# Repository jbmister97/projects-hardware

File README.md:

View this project on [CADLAB.io](https://cadlab.io/project/2418). 

# projects-hardware

A collection of personal schematics and PCB design projects done using various EDA tools. Most of the projects are done using KiCad software with the exceptions of the following projects:

Arduino_Nanite_85   - Altium CircuitMaker
      
These projects can be downloaded and viewed using their respective EDA tools.

NOTE: Some of these projects may be unfinished and the ones that are in progress may be found in a separate branch and not in master. Switch to that branch to view the project.

Finished:

-NRF52 Reference

      Known issue: Low battery indicator not functioning properly. It is on when battery is high and off when battery is low.
      
-Buck converter V1

-Outlet Relay V1

-USB Type A Breakout V1

In progress:

-NRF52 V2

-4-Channel Motor controller

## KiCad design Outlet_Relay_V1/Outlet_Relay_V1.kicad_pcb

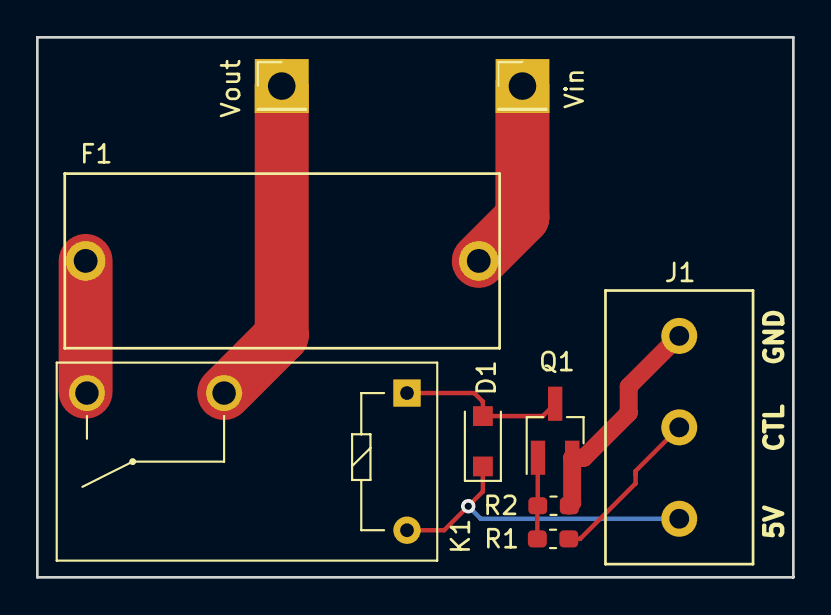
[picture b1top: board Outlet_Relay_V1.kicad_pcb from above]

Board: 2 copper layers, 42.0 x 30.0 mm, 9 parts (0 on the bottom side), 8 nets.

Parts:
D1: BAS116H,115; D_SOD-123F
F1: Fuse; Fuse_Holder_Keystone_4527_Cartridge
J1: TerminalBlock_1x3_5.08mmPitch; TerminalBlock_Molex_1x3_5.04mmPitch
K1: G5Q-1A; Relay_SPST_Omron-G5Q-1A
Q1: BSS138K; SOT-23_Handsoldering
R1: 1k; R_0603_1608Metric_Pad1.05x0.95mm_HandSolder
R2: 10k; R_0603_1608Metric_Pad1.05x0.95mm_HandSolder
Vin: PinHeader_1x01_P2.54mm_Vertical
Vout: PinHeader_1x01_P2.54mm_Vertical

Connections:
/5V: D1.1, J1.1, K1.5
/CTL: J1.2, R1.1
GND: J1.3, Q1.2, R2.2
unnamed: D1.2, K1.1, Q1.3
unnamed: F1.1, K1.3
unnamed: Q1.1, R1.2, R2.1
Vin: F1.2, Vin.1
Vout: K1.2, Vout.1

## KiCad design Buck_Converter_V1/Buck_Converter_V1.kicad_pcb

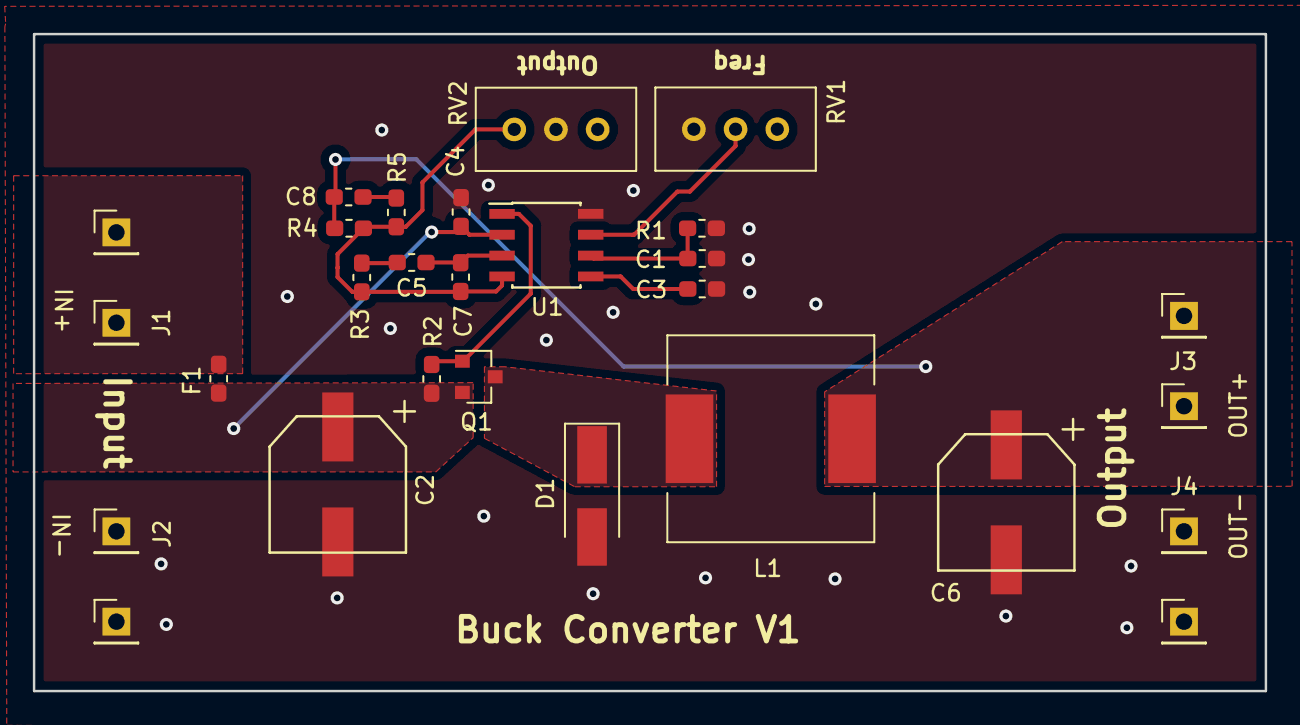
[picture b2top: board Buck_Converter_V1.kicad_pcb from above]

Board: 2 copper layers, 75.0 x 40.0 mm, 28 parts (0 on the bottom side), 13 nets.

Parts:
C1, C4: 0.1uF; C_0603_1608Metric_Pad1.05x0.95mm_HandSolder
C2, C6: 180uF; C_AlPo_Radial_SMT_8.3mmx8.3mm
C3: 1uF; C_0603_1608Metric_Pad1.05x0.95mm_HandSolder
C5: 6.8nF; C_0603_1608Metric_Pad1.05x0.95mm_HandSolder
C7: 68pF; C_0603_1608Metric_Pad1.05x0.95mm_HandSolder
C8: 4.7nF; C_0603_1608Metric_Pad1.05x0.95mm_HandSolder
D1: NRVTSA4100ET3G; D_SMA_Handsoldering
F1: Fuse; Fuse_0603_1608Metric_Pad1.05x0.95mm_HandSolder
IN+: PinHeader_1x01_P2.54mm_Vertical
IN-: PinHeader_1x01_P2.54mm_Vertical
J1, J2, J3, J4: Conn_01x01_Male; PinHeader_1x01_P2.54mm_Vertical
L1: 33uH; L_12x12mm_H8mm
OUT+: PinHeader_1x01_P2.54mm_Vertical
OUT-: PinHeader_1x01_P2.54mm_Vertical
Q1: SI2319CDS-T1-GE3; SOT-23
R1: 56k; R_0603_1608Metric_Pad1.05x0.95mm_HandSolder
R2: 3k; R_0603_1608Metric_Pad1.05x0.95mm_HandSolder
R3: 14.9k; R_0603_1608Metric_Pad1.05x0.95mm_HandSolder
R4: 16.5k; R_0603_1608Metric_Pad1.05x0.95mm_HandSolder
R5: 383; R_0603_1608Metric_Pad1.05x0.95mm_HandSolder
RV1: 25k; Potentiometer_Bourns_3296W_Vertical
RV2: 4125; Potentiometer_Bourns_3296W_Vertical
U1: TL5001CDR; SOIC-8_3.9x4.9mm_P1.27mm

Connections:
GND: C1.2, C2.2, C3.1, C4.2, C6.2, D1.2, IN-.1, J2.1, J4.1, OUT-.1, R1.2, RV1.1, RV2.2, U1.8
unnamed: C1.1, R1.1, U1.6
unnamed: C3.2, U1.5
unnamed: C5.1, R3.2
unnamed: C5.2, C7.2, U1.3
unnamed: C7.1, R3.1, R4.2, R5.2, RV2.1, U1.4
unnamed: C8.2, R5.1
unnamed: D1.1, L1.1, Q1.3
unnamed: F1.2, IN+.1, J1.1
unnamed: RV1.2, U1.7
P_DRIVE: Q1.1, R2.1, U1.1
Vin: C2.1, C4.1, F1.1, Q1.2, R2.2, U1.2
Vout: C6.1, C8.1, J3.1, L1.2, OUT+.1, R4.1

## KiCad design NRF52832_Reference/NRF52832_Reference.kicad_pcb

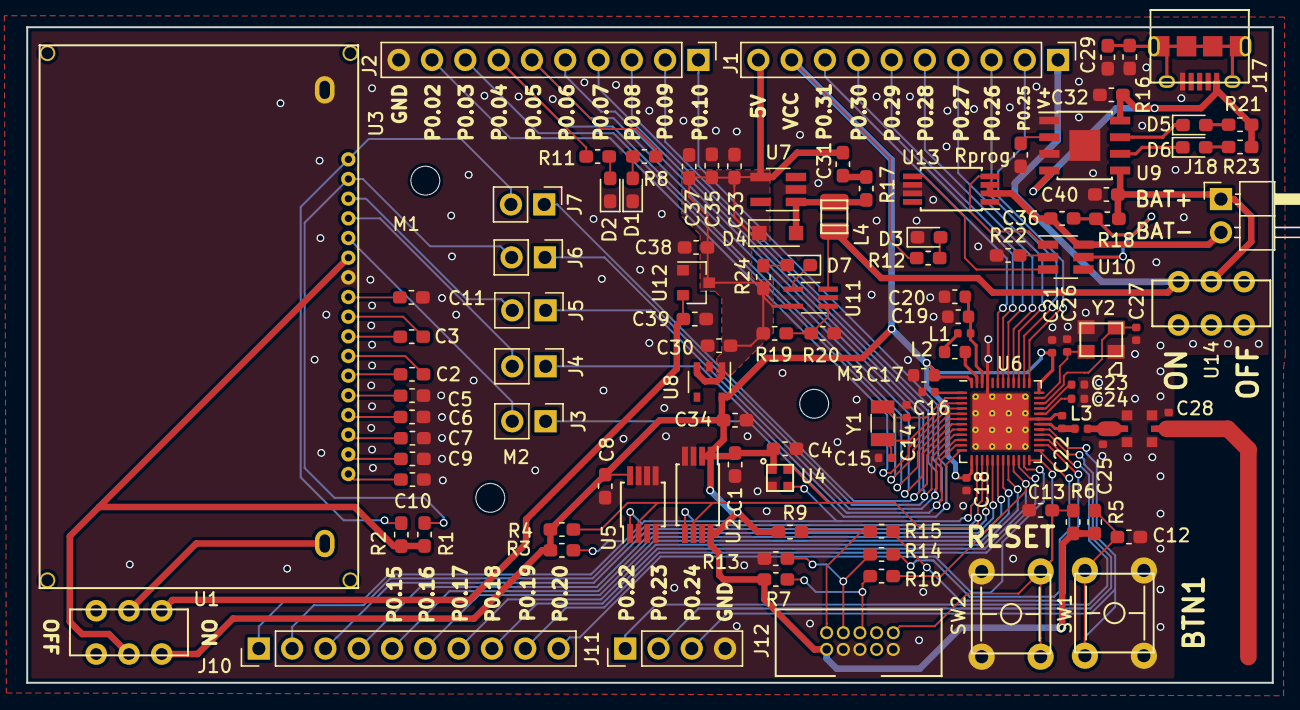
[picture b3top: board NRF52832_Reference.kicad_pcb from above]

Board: 2 copper layers, 95.0 x 50.0 mm, 110 parts (0 on the bottom side), 91 nets.

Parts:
C1, C4, C8, C12, C13, C29, C36: 0.1uF; C_0603_1608Metric_Pad1.05x0.95mm_HandSolder
C2, C3, C5, C6, C7, C9, C10, C11, C30, C34, C38: 1uF; C_0603_1608Metric_Pad1.05x0.95mm_HandSolder
C14, C15: 14pF; C_0402_1005Metric
C16, C18, C21: 100nF; C_0402_1005Metric
C17: 4.7uF; C_0603_1608Metric
C19: 1.0uF; C_0603_1608Metric
C20: N.C.; C_0603_1608Metric
C22: 0.8pF; C_0402_1005Metric
C23: 100pF; C_0402_1005Metric
C24, C25: N.C.; C_0402_1005Metric
C26: 12pF; C_0402_1005Metric
C27: 12nF; C_0402_1005Metric
C28: 1.2pF; C_0402_1005Metric
C31: 120pF; C_0603_1608Metric_Pad1.05x0.95mm_HandSolder
C32, C33, C35, C37, C40: 10uF; C_0603_1608Metric_Pad1.05x0.95mm_HandSolder
C39: 4.7uF; C_0603_1608Metric_Pad1.05x0.95mm_HandSolder
D1, D2, D3, D5, D6, D7: LED; LED_0603_1608Metric_Pad1.05x0.95mm_HandSolder
D4: D_Schottky; D_SOD-123F
J1, J2, J10: Conn_01x10_Male; PinHeader_1x10_P2.54mm_Vertical
J3, J4, J5, J6, J7: Conn_01x02_Male; PinHeader_1x02_P2.54mm_Vertical
J11: Conn_01x04_Male; PinHeader_1x04_P2.54mm_Vertical
J12: SWD_Header; SWD_Header_CNC_Tech_3220-10-0100-00
J16: MM8130-2600RA2; MURATA_MM8130-2600RA2
J17: USB_B_Micro; USB_Micro_B_Amphenol_10118194-0001LF
J18: Conn_01x02_Male; PinHeader_1x02_P2.54mm_Horizontal
L1: 15nH; L_0402_1005Metric
L2: 10uH; L_0603_1608Metric
L3: 3.9nH; L_0402_1005Metric
L4: 2.2uH; L_1008_2520Metric
M1, M2, M3: MountingHole_2.2mm_M2
R1, R2, R7, R9, R13, R16: 10k; R_0603_1608Metric_Pad1.05x0.95mm_HandSolder
R3, R4: 4.7k; R_0603_1608Metric_Pad1.05x0.95mm_HandSolder
R5, R6: 47k; R_0603_1608Metric_Pad1.05x0.95mm_HandSolder
R8, R11, R12, R18: 100; R_0603_1608Metric_Pad1.05x0.95mm_HandSolder
R10, R14, R15: 22; R_0603_1608Metric_Pad1.05x0.95mm_HandSolder
R17: 5.6; R_0603_1608Metric_Pad1.05x0.95mm_HandSolder
R19: 100k; R_0603_1608Metric_Pad1.05x0.95mm_HandSolder
R20: 220k; R_0603_1608Metric_Pad1.05x0.95mm_HandSolder
R21, R23: 300; R_0603_1608Metric_Pad1.05x0.95mm_HandSolder
R22: 1k; R_0603_1608Metric_Pad1.05x0.95mm_HandSolder
R24: 220; R_0603_1608Metric_Pad1.05x0.95mm_HandSolder
Rprog: 1.2k; R_0603_1608Metric_Pad1.05x0.95mm_HandSolder
SW1, SW2: Button; SW_Tactile_TE_1825910-6
U1, U14: SLIDE_SW_DPDT; SW_DPDT_Slide_JS202011CQN
U2: AT34C04-X5M-T; TSSOP-8_4.4x3mm_P0.65mm
U3: NHD-C12832A1Z-NSW-BBW-3V3; LCD_NHD-C12832A1Z-NSW-BBW-3V3
U4: LTR-329ALS-01; Sensor_Photo_LTR-329ALS-01
U5: TCN75AVUA713; MSOP-8_3x3mm_P0.65mm
U6: nRF52832; QFN-48-1EP_6x6mm_P0.4mm_EP4.3x4.3mm_ThermalVias
U7: TPS613222ADBVR; SOT-23-5_HandSoldering
U8: NCV8161BSN330T1G; TSOP-5_1.65x3.05mm_P0.95mm
U9: TP4056E-SN2L1P; SOIC-8-1EP_3.9x4.9mm_P1.27mm_EP2.35x2.35mm
U10: DW01; SOT-23-6_Handsoldering
U11: LMV331ICT; SOT-353_SC-70-5_Handsoldering
U12: AP2138N-3.0TRG1; SOT-23
U13: FS8205A; TSSOP-8_4.4x3mm_P0.65mm
Y1: 32.768kHz; Crystal_SMD_3215-2Pin_3.2x1.5mm
Y2: 32MHz; Crystal_32MHz_Kyocera_CX3225SB32000D0FFFCC

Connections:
3V3_Ref: C1.1, C4.1, C8.1, C17.1, C18.1, C21.1, C34.1, J1.9, J12.1, R3.1, R4.1, R5.1, R6.1, R7.1, R9.1, R12.1, U1.3, U2.1, U2.2, U2.8, U4.1, U5.8, U6.13, U6.36, U6.48, U8.5
3V_Ref: C39.1, U1.6, U12.2
5V_Ref: C30.1, C31.1, C33.1, C35.1, C37.1, C38.1, D4.1, J1.10, R19.1, R24.1, U7.4, U8.1, U8.3, U11.5, U12.3
/Sheet5BF15571/ANT: C28.1, J16.OUT
/Sheet5BF15571/RF: C25.1, J16.IN, L3.2
/Sheet5BF15571/SWDCLK: R14.2, U6.25
/Sheet5BF15571/SWDIO: R15.2, U6.26
GND: C1.2, C4.2, C5.2, C6.2, C7.2, C8.2, C9.2, C10.2, C11.2, C12.2, C13.2, C14.2, C15.2, C16.2, C17.2, C18.2, C19.2, C20.2, C21.2, C22.2, C23.1, C24.1, C25.2, C26.1, C27.1, C28.2, C29.2, C30.2, C32.2, C33.2, C34.2, C35.2, C37.2, C38.2, C39.2, C40.2, D1.1, D2.1, D3.1, J2.10, J11.4, J12.3, J12.5, J12.9, J16.GND1, J16.GND2, J16.GND3, J16.GND4, J17.5, R13.2, R16.2, R20.2, R22.2, Rprog.2, SW1.3, SW1.4, SW2.3, SW2.4, U2.3, U2.4, U3.11, U3.19, U4.2, U5.4, U5.5, U5.6, U5.7, U6.31, U6.45, U6.49, U7.2, U8.2, U9.1, U9.3, U9.9, U11.2, U12.1, U13.6, U13.7, Y2.2, Y2.4
unnamed: C2.1, U3.6
unnamed: C2.2, U3.7
unnamed: C3.1, U3.9
unnamed: C3.2, U3.8
unnamed: C5.1, U3.5
unnamed: C6.1, U3.4
unnamed: C7.1, U3.3
unnamed: C9.1, U3.2
unnamed: C10.1, U3.1
unnamed: C11.1, U3.10
unnamed: C14.1, U6.2, Y1.1
unnamed: C15.1, U6.3, Y1.2
unnamed: C16.1, U6.1
unnamed: C19.1, C20.1, L1.2, U6.46
unnamed: C22.1, L3.1, U6.30
unnamed: C23.2, U6.33
unnamed: C24.2, U6.32
unnamed: C26.2, U6.35, Y2.1
unnamed: C27.2, U6.34, Y2.3
unnamed: C29.1, J17.6, R16.1
unnamed: C31.2, R17.1
unnamed: C32.1, J17.1, R21.1, R23.1, U9.4, U9.8
unnamed: C36.1, R18.1, U10.5
unnamed: C36.2, J18.2, U10.6, U13.2, U13.3
unnamed: C40.1, J18.1, R18.2, U9.5, U14.2
unnamed: D1.2, R8.2
unnamed: D2.2, R11.2
unnamed: D3.2, R12.2
unnamed: D4.2, L4.2, R17.2, U7.1
unnamed: D5.1, U9.7
unnamed: D5.2, R21.2
unnamed: D6.1, U9.6
unnamed: D6.2, R23.2
unnamed: D7.1, U11.4
unnamed: D7.2, R24.2
unnamed: J3.2, U3.13
unnamed: J4.2, U3.14
unnamed: J5.2, U3.15
unnamed: J6.2, R1.2, U3.16
unnamed: J7.2, R2.2, U3.17
unnamed: J12.2, R9.2, R15.1
unnamed: J12.4, R13.1, R14.1
unnamed: J12.6, R7.2, R10.2
unnamed: L1.1, L2.2
unnamed: L2.1, U6.47
unnamed: R1.1, R2.1, U1.2, U3.12
unnamed: R19.2, R20.1, U11.1
unnamed: R22.1, U10.2
unnamed: Rprog.1, U9.2
unnamed: U1.5, U3.18
unnamed: U10.1, U13.4
unnamed: U10.3, U13.5
P0.02: J2.9, U6.4
P0.03: J2.8, U6.5
P0.04: J2.7, R11.1, U6.6
P0.05: J2.6, R8.1, U6.7
P0.06_CS1: J2.5, J7.1, U6.8
P0.07_RES: J2.4, J6.1, U6.9
P0.08_A0: J2.3, J5.1, U6.10
P0.09_SCL: J2.2, J4.1, U6.11
P0.10_SI: J2.1, J3.1, U6.12
P0.11_SDA: J10.1, R3.2, U2.5, U4.3, U5.1, U6.14
P0.12_SCL: J10.2, R4.2, U2.6, U4.4, U5.2, U6.15
P0.13: J10.3, U6.16
P0.14: J10.4, U6.17
P0.15: J10.5, U6.18
P0.16: J10.6, U6.19
P0.17: J10.7, U6.20
P0.18_SWO: J10.8, R10.1, U6.21
P0.19: J10.9, U6.22
P0.20: J10.10, U6.23
P0.22: J11.1, U6.27
P0.23: J11.2, U6.28
P0.24: C12.1, J11.3, R5.2, SW1.1, SW1.2, U6.29
P0.25: J1.2, U6.37
P0.26: J1.3, U6.38
P0.27: J1.4, U6.39
P0.28: J1.5, U6.40
P0.29: J1.6, U6.41
P0.30: J1.7, U6.42
P0.31: J1.8, U6.43
RESET: C13.1, J12.10, R6.2, SW2.1, SW2.2, U6.24
V+: J1.1, L4.1, U11.3, U14.3

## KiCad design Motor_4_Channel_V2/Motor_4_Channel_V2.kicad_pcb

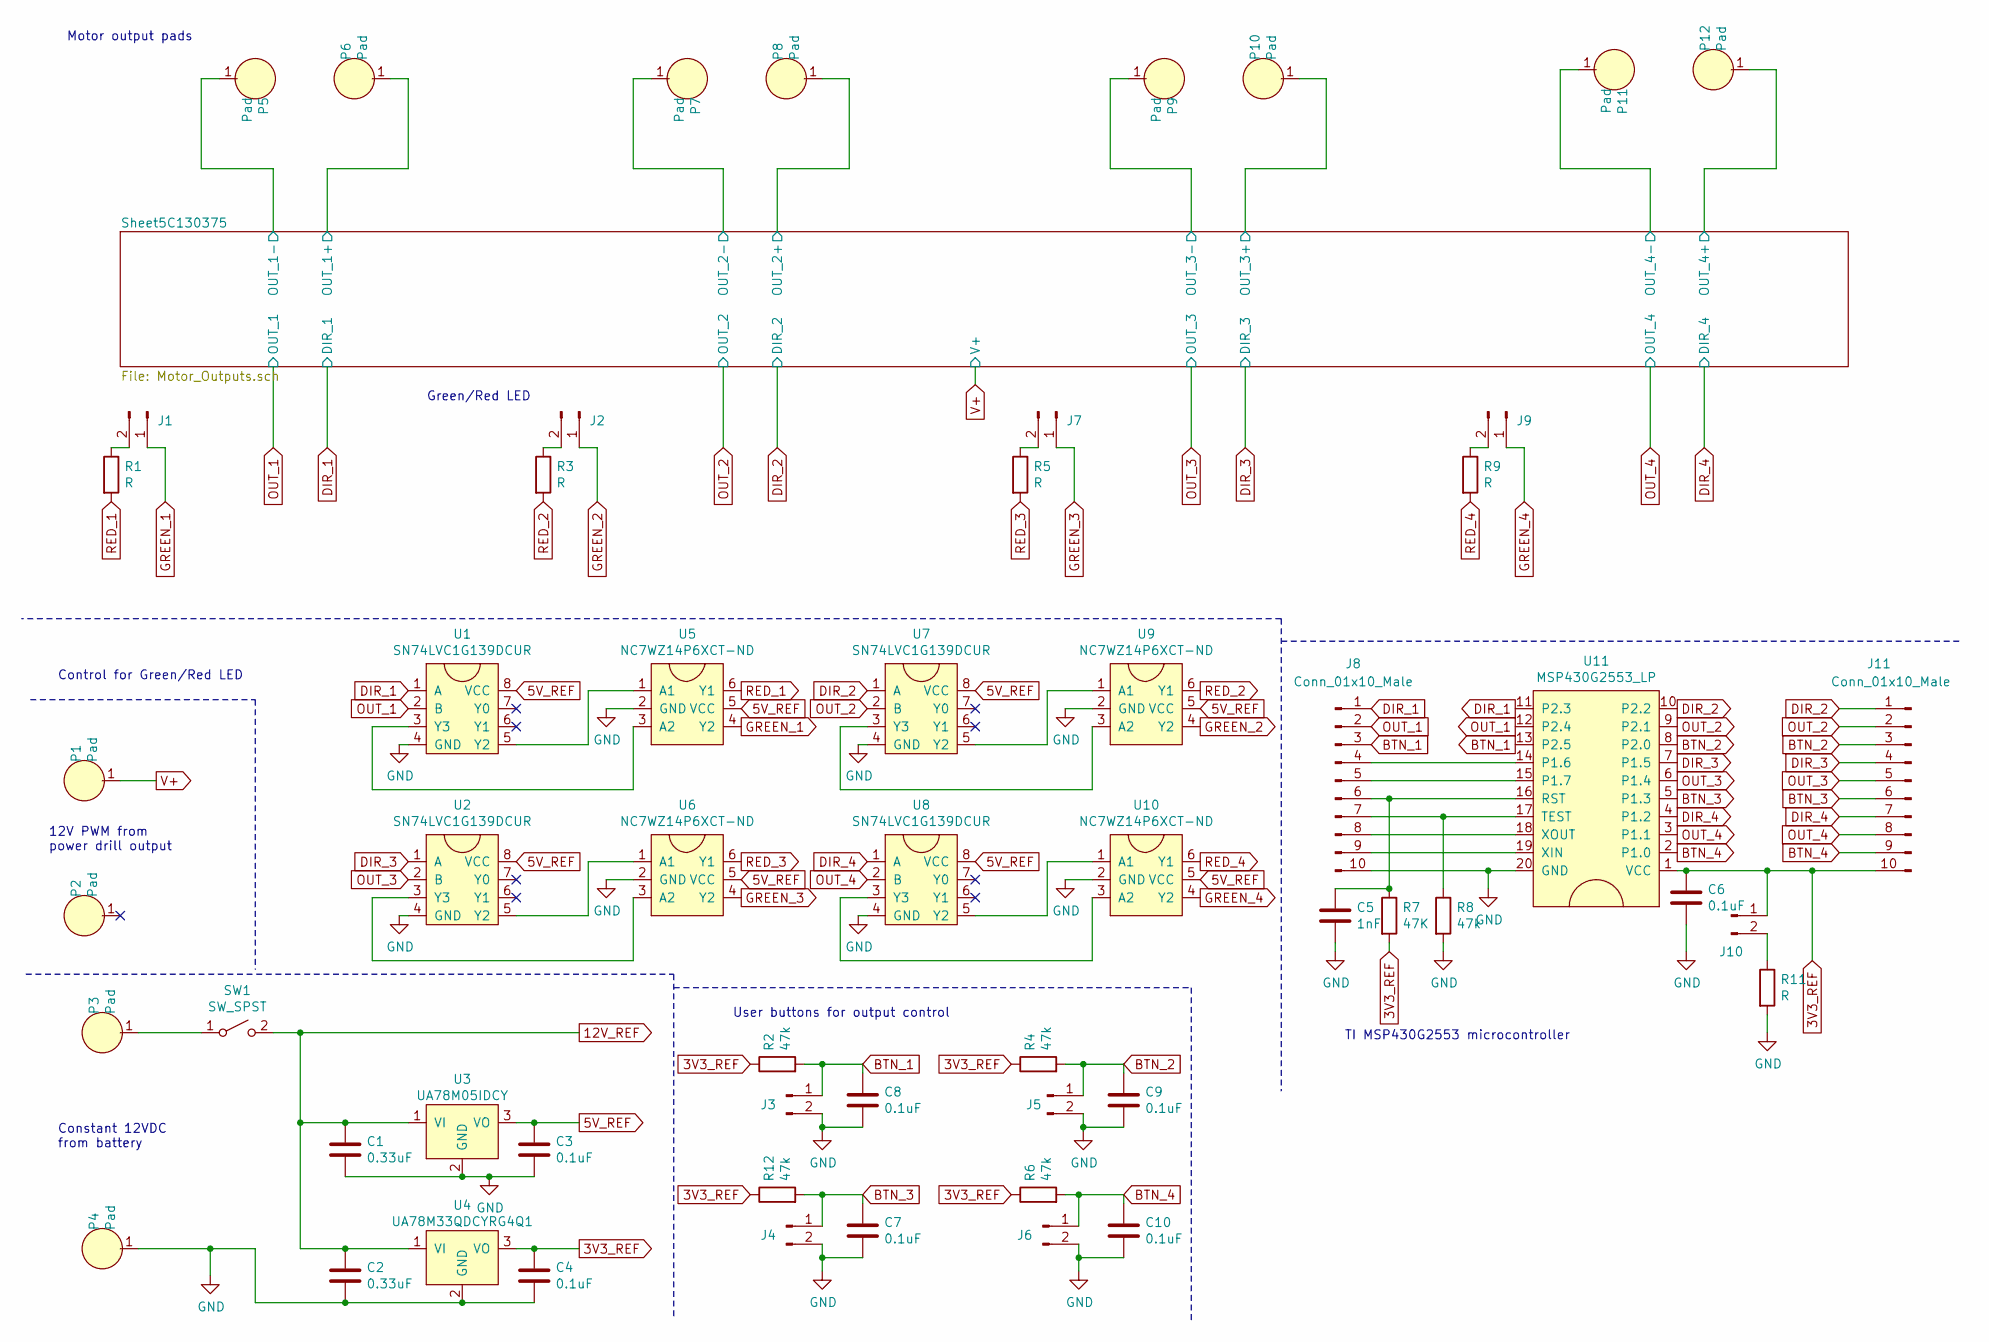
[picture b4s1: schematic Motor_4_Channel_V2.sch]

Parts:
C1, C2: 0.33uF; C_0603_1608Metric_Pad1.05x0.95mm_HandSolder
C3, C4, C6, C7, C8, C9, C10: 0.1uF; C_0603_1608Metric_Pad1.05x0.95mm_HandSolder
C5: 1nF; C_0603_1608Metric_Pad1.05x0.95mm_HandSolder
J1, J2, J3, J4, J5, J6, J7, J9, J10: Conn_01x02_Male; PinHeader_1x02_P2.54mm_Vertical_SMD_Pin1Left
J8, J11: Conn_01x10_Male; PinHeader_1x10_P2.54mm_Vertical
P1, P2, P3, P4, P5, P6, P7, P8, P9, P10, P11, P12: Pad
R1, R3, R5, R9, R11: R; R_0603_1608Metric_Pad1.05x0.95mm_HandSolder
R2, R4, R6, R8, R12: 47k; R_0603_1608Metric_Pad1.05x0.95mm_HandSolder
R7: 47K; R_0603_1608Metric_Pad1.05x0.95mm_HandSolder
SW1: SW_SPST; PinHeader_1x02_P2.54mm_Vertical
U1, U2, U7, U8: SN74LVC1G139DCUR; VSSOP-8_2.4x2.1mm_P0.5mm
U3: UA78M05IDCY; SOT-223-3_TabPin2
U4: UA78M33QDCYRG4Q1; SOT-223-3_TabPin2
U5, U6, U9, U10: NC7WZ14P6XCT-ND; SC-70-6
U11: MSP430G2553_LP; DIP-20_W7.62mm_Socket_LongPads

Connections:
3V3_REF: C4.1, C6.1, J10.1, J11.10, R2.1, R4.1, R6.1, R7.2, R12.1, U4.3 (VO), U11.1 (VCC)
5V_REF: C3.1, U1.8 (VCC), U2.8 (VCC), U3.3 (VO), U5.5 (VCC), U6.5 (VCC), U7.8 (VCC), U8.8 (VCC), U9.5 (VCC), U10.5 (VCC)
12V_REF: C1.1, C2.1, SW1.2 (B), U3.1 (VI), U4.1 (VI); also elsewhere on the board
/Sheet5C130375/OUT_1+: P6.1; also elsewhere on the board
/Sheet5C130375/OUT_1-: P5.1; also elsewhere on the board
/Sheet5C130375/OUT_2+: P8.1; also elsewhere on the board
/Sheet5C130375/OUT_2-: P7.1; also elsewhere on the board
/Sheet5C130375/OUT_3+: P10.1; also elsewhere on the board
/Sheet5C130375/OUT_3-: P9.1; also elsewhere on the board
/Sheet5C130375/OUT_4+: P12.1; also elsewhere on the board
/Sheet5C130375/OUT_4-: P11.1; also elsewhere on the board
BTN_1: C8.1, J3.1, J8.3, R2.2, U11.13 (P2.5)
BTN_2: C9.1, J5.1, J11.3, R4.2, U11.8 (P2.0)
BTN_3: C7.1, J4.1, J11.6, R12.2, U11.5 (P1.3)
BTN_4: C10.1, J6.1, J11.9, R6.2, U11.2 (P1.0)
DIR_1: J8.1, U1.1 (A), U11.11 (P2.3); also elsewhere on the board
DIR_2: J11.1, U7.1 (A), U11.10 (P2.2); also elsewhere on the board
DIR_3: J11.4, U2.1 (A), U11.7 (P1.5); also elsewhere on the board
DIR_4: J11.7, U8.1 (A), U11.4 (P1.2); also elsewhere on the board
GND: C1.2, C2.2, C3.2, C4.2, C5.2, C6.2, C7.2, C8.2, C9.2, C10.2, J3.2, J4.2, J5.2, J6.2, J8.10, P4.1, R8.2, R11.2, U1.4 (GND), U2.4 (GND), U3.2 (GND), U4.2 (GND), U5.2 (GND), U6.2 (GND), U7.4 (GND), U8.4 (GND), U9.2 (GND), U10.2 (GND), U11.20 (GND); also elsewhere on the board
GREEN_1: J1.1, U5.4 (Y2)
GREEN_2: J2.1, U9.4 (Y2)
GREEN_3: J7.1, U6.4 (Y2)
GREEN_4: J9.1, U10.4 (Y2); also elsewhere on the board
unnamed: C5.1, J8.6, R7.1, U11.16 (RST)
unnamed: J1.2, R1.1
unnamed: J2.2, R3.1
unnamed: J7.2, R5.1
unnamed: J8.4, U11.14 (P1.6)
unnamed: J8.5, U11.15 (P1.7)
unnamed: J8.7, R8.1, U11.17 (TEST)
unnamed: J8.8, U11.18 (XOUT)
unnamed: J8.9, U11.19 (XIN)
unnamed: J9.2, R9.1
unnamed: J10.2, R11.1
unnamed: P3.1, SW1.1 (A)
unnamed: U1.3 (Y3), U5.3 (A2)
unnamed: U1.5 (Y2), U5.1 (A1)
unnamed: U2.3 (Y3), U6.3 (A2)
unnamed: U2.5 (Y2), U6.1 (A1)
unnamed: U7.3 (Y3), U9.3 (A2)
unnamed: U7.5 (Y2), U9.1 (A1)
unnamed: U8.5 (Y2), U10.1 (A1)
unnamed: U8.3 (Y3), U10.3 (A2)
OUT_1: J8.2, U1.2 (B), U11.12 (P2.4); also elsewhere on the board
OUT_2: J11.2, U7.2 (B), U11.9 (P2.1); also elsewhere on the board
OUT_3: J11.5, U2.2 (B), U11.6 (P1.4); also elsewhere on the board
OUT_4: J11.8, U8.2 (B), U11.3 (P1.1); also elsewhere on the board
RED_1: R1.2, U5.6 (Y1)
RED_2: R3.2, U9.6 (Y1)
RED_3: R5.2, U6.6 (Y1)
RED_4: R9.2, U10.6 (Y1)
V+: P1.1; also elsewhere on the board

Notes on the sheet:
Constant 12VDC from battery
12V PWM from power drill output
Control for Green/Red LED
User buttons for output control
TI MSP430G2553 microcontroller
Green/Red LED
Motor output pads

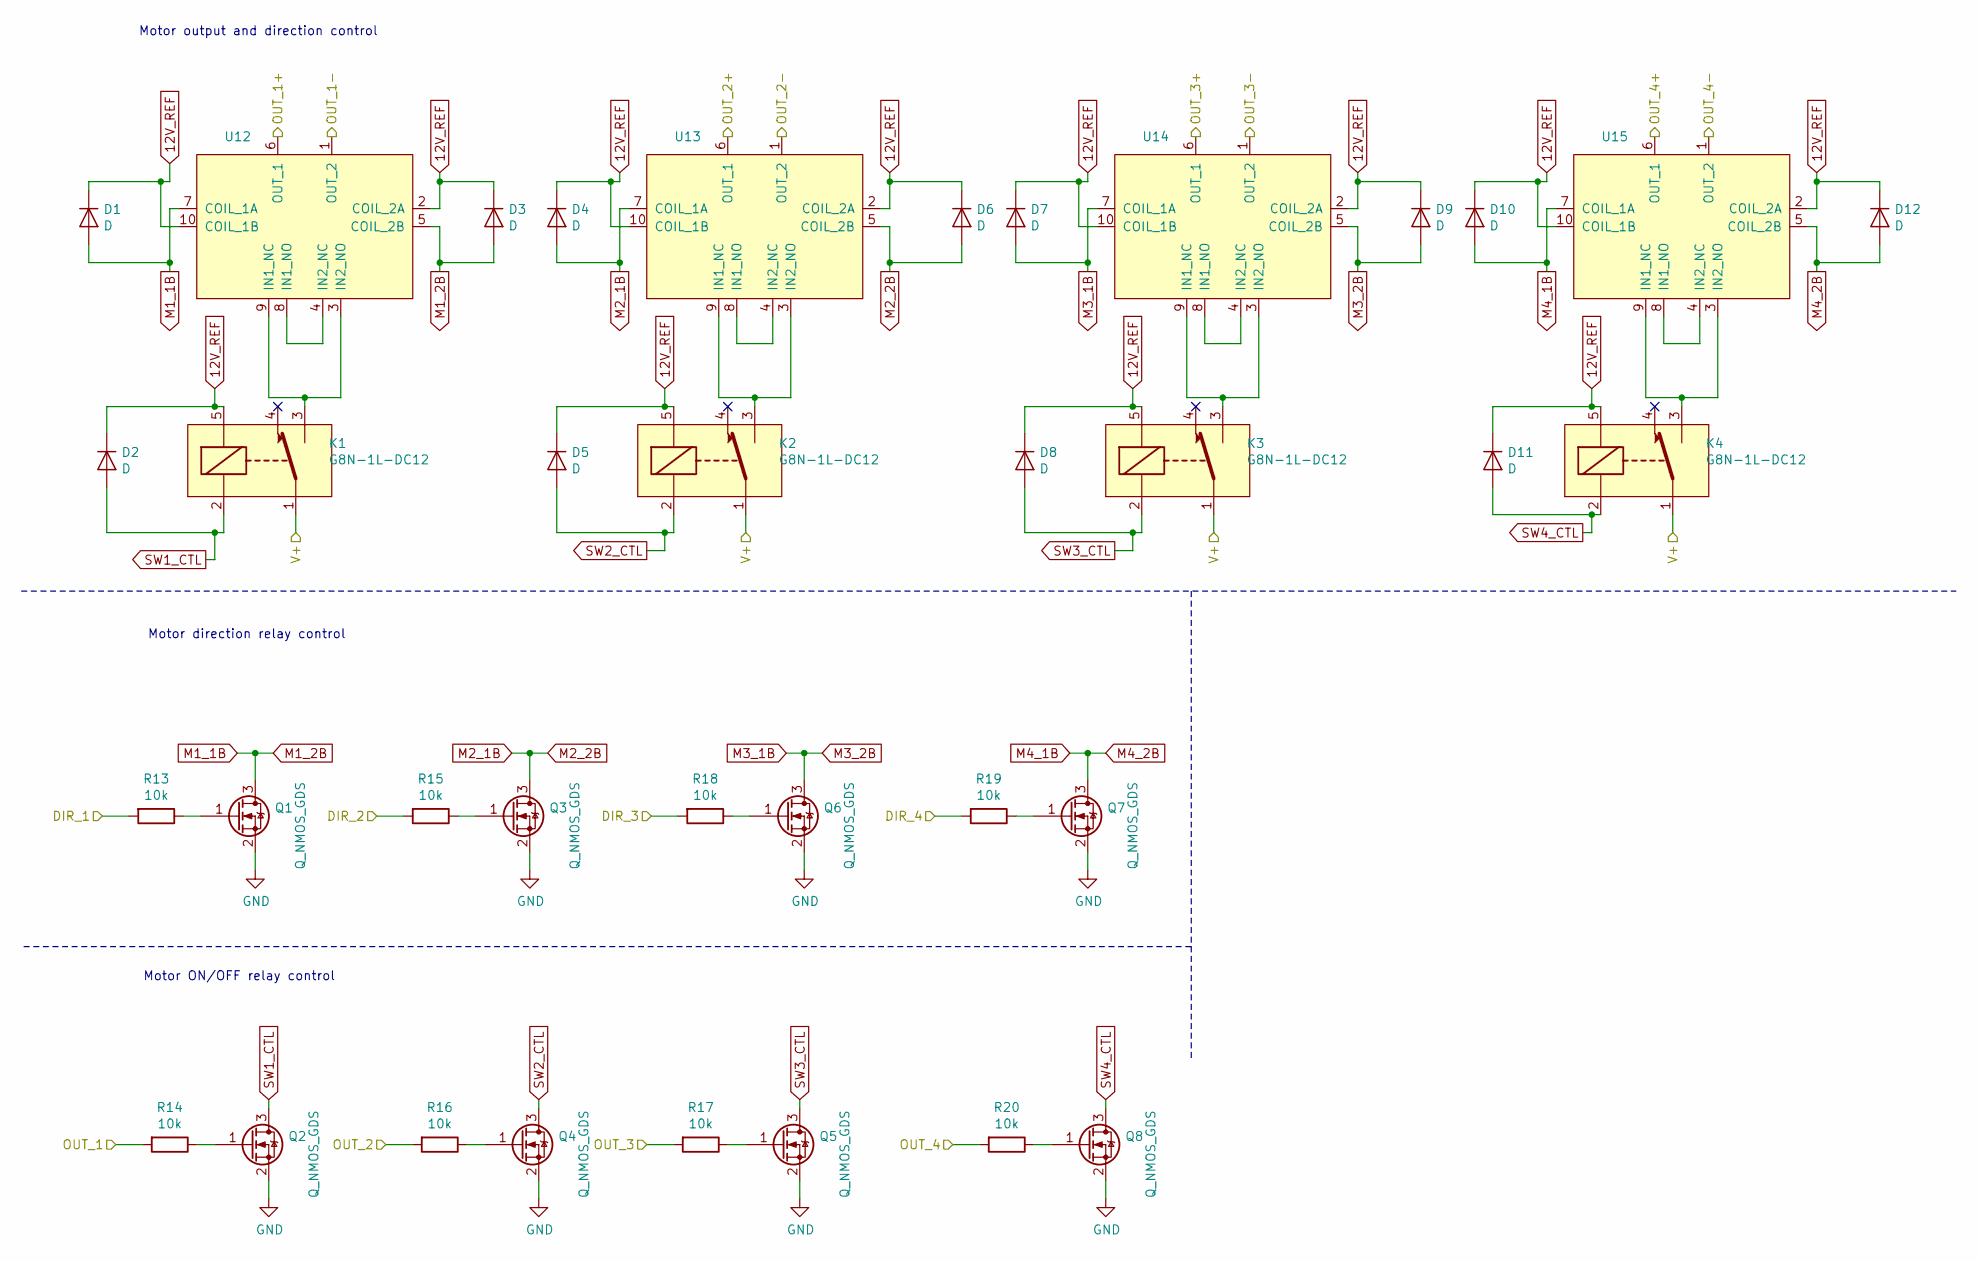
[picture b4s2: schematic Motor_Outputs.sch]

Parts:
D1, D2, D3, D4, D5, D6, D7, D8, D9, D10, D11, D12: D; DO-214AC
K1, K2, K3, K4: G8N-1L-DC12
Q1, Q2, Q3, Q4, Q5, Q6, Q7, Q8: Q_NMOS_GDS; SOT-23
R13, R14, R15, R16, R17, R18, R19, R20: 10k; R_0603_1608Metric_Pad1.05x0.95mm_HandSolder
U12, U13, U14, U15: G8NW-2H-DC12

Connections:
12V_REF: D1.1 (K), D2.1 (K), D3.1 (K), D4.1 (K), D5.1 (K), D6.1 (K), D7.1 (K), D8.1 (K), D9.1 (K), D10.1 (K), D11.1 (K), D12.1 (K), K1.5, K2.5, K3.5, K4.5, U12.2 (COIL_2A), U12.10 (COIL_1B), U13.2 (COIL_2A), U13.10 (COIL_1B), U14.2 (COIL_2A), U14.10 (COIL_1B), U15.2 (COIL_2A), U15.10 (COIL_1B); also elsewhere on the board
/Sheet5C130375/OUT_1+: U12.1 (OUT_2); also elsewhere on the board
/Sheet5C130375/OUT_1-: U12.6 (OUT_1); also elsewhere on the board
/Sheet5C130375/OUT_2+: U13.1 (OUT_2); also elsewhere on the board
/Sheet5C130375/OUT_2-: U13.6 (OUT_1); also elsewhere on the board
/Sheet5C130375/OUT_3+: U14.1 (OUT_2); also elsewhere on the board
/Sheet5C130375/OUT_3-: U14.6 (OUT_1); also elsewhere on the board
/Sheet5C130375/OUT_4+: U15.1 (OUT_2); also elsewhere on the board
/Sheet5C130375/OUT_4-: U15.6 (OUT_1); also elsewhere on the board
DIR_1: R13.2; also elsewhere on the board
DIR_2: R15.2; also elsewhere on the board
DIR_3: R18.2; also elsewhere on the board
DIR_4: R19.2; also elsewhere on the board
GND: Q1.2 (S), Q2.2 (S), Q3.2 (S), Q4.2 (S), Q5.2 (S), Q6.2 (S), Q7.2 (S), Q8.2 (S); also elsewhere on the board
M1_1B: D1.2 (A), D3.2 (A), Q1.3 (D), U12.5 (COIL_2B), U12.7 (COIL_1A)
M2_1B: D4.2 (A), D6.2 (A), Q3.3 (D), U13.5 (COIL_2B), U13.7 (COIL_1A)
M3_1B: D7.2 (A), D9.2 (A), Q6.3 (D), U14.5 (COIL_2B), U14.7 (COIL_1A)
M4_1B: D10.2 (A), D12.2 (A), Q7.3 (D), U15.5 (COIL_2B), U15.7 (COIL_1A)
unnamed: K1.3, U12.3 (IN2_NO), U12.9 (IN1_NC)
unnamed: K2.3, U13.3 (IN2_NO), U13.9 (IN1_NC)
unnamed: K3.3, U14.3 (IN2_NO), U14.9 (IN1_NC)
unnamed: K4.3, U15.3 (IN2_NO), U15.9 (IN1_NC)
unnamed: Q1.1 (G), R13.1
unnamed: Q2.1 (G), R14.1
unnamed: Q3.1 (G), R15.1
unnamed: Q4.1 (G), R16.1
unnamed: Q5.1 (G), R17.1
unnamed: Q6.1 (G), R18.1
unnamed: Q7.1 (G), R19.1
unnamed: Q8.1 (G), R20.1
unnamed: U12.4 (IN2_NC), U12.8 (IN1_NO)
unnamed: U13.4 (IN2_NC), U13.8 (IN1_NO)
unnamed: U14.4 (IN2_NC), U14.8 (IN1_NO)
unnamed: U15.4 (IN2_NC), U15.8 (IN1_NO)
OUT_1: R14.2; also elsewhere on the board
OUT_2: R16.2; also elsewhere on the board
OUT_3: R17.2; also elsewhere on the board
OUT_4: R20.2; also elsewhere on the board
SW1_CTL: D2.2 (A), K1.2, Q2.3 (D)
SW2_CTL: D5.2 (A), K2.2, Q4.3 (D)
SW3_CTL: D8.2 (A), K3.2, Q5.3 (D)
SW4_CTL: D11.2 (A), K4.2, Q8.3 (D)
V+: K1.1, K2.1, K3.1, K4.1; also elsewhere on the board

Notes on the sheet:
Motor output and direction control
Motor direction relay control
Motor ON/OFF relay control

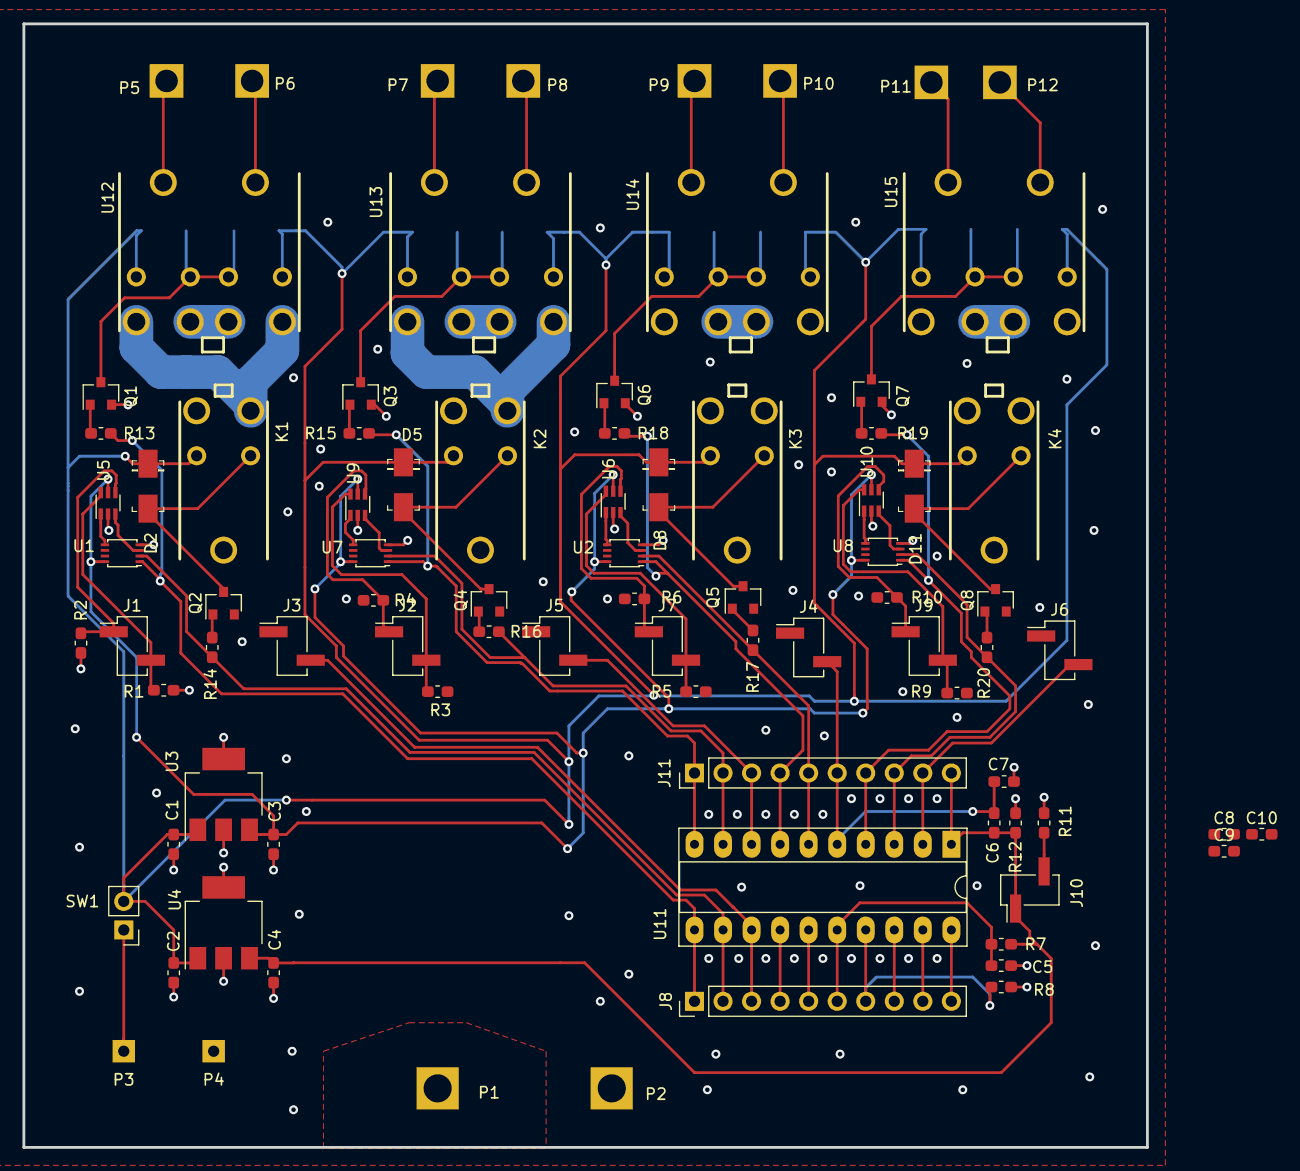
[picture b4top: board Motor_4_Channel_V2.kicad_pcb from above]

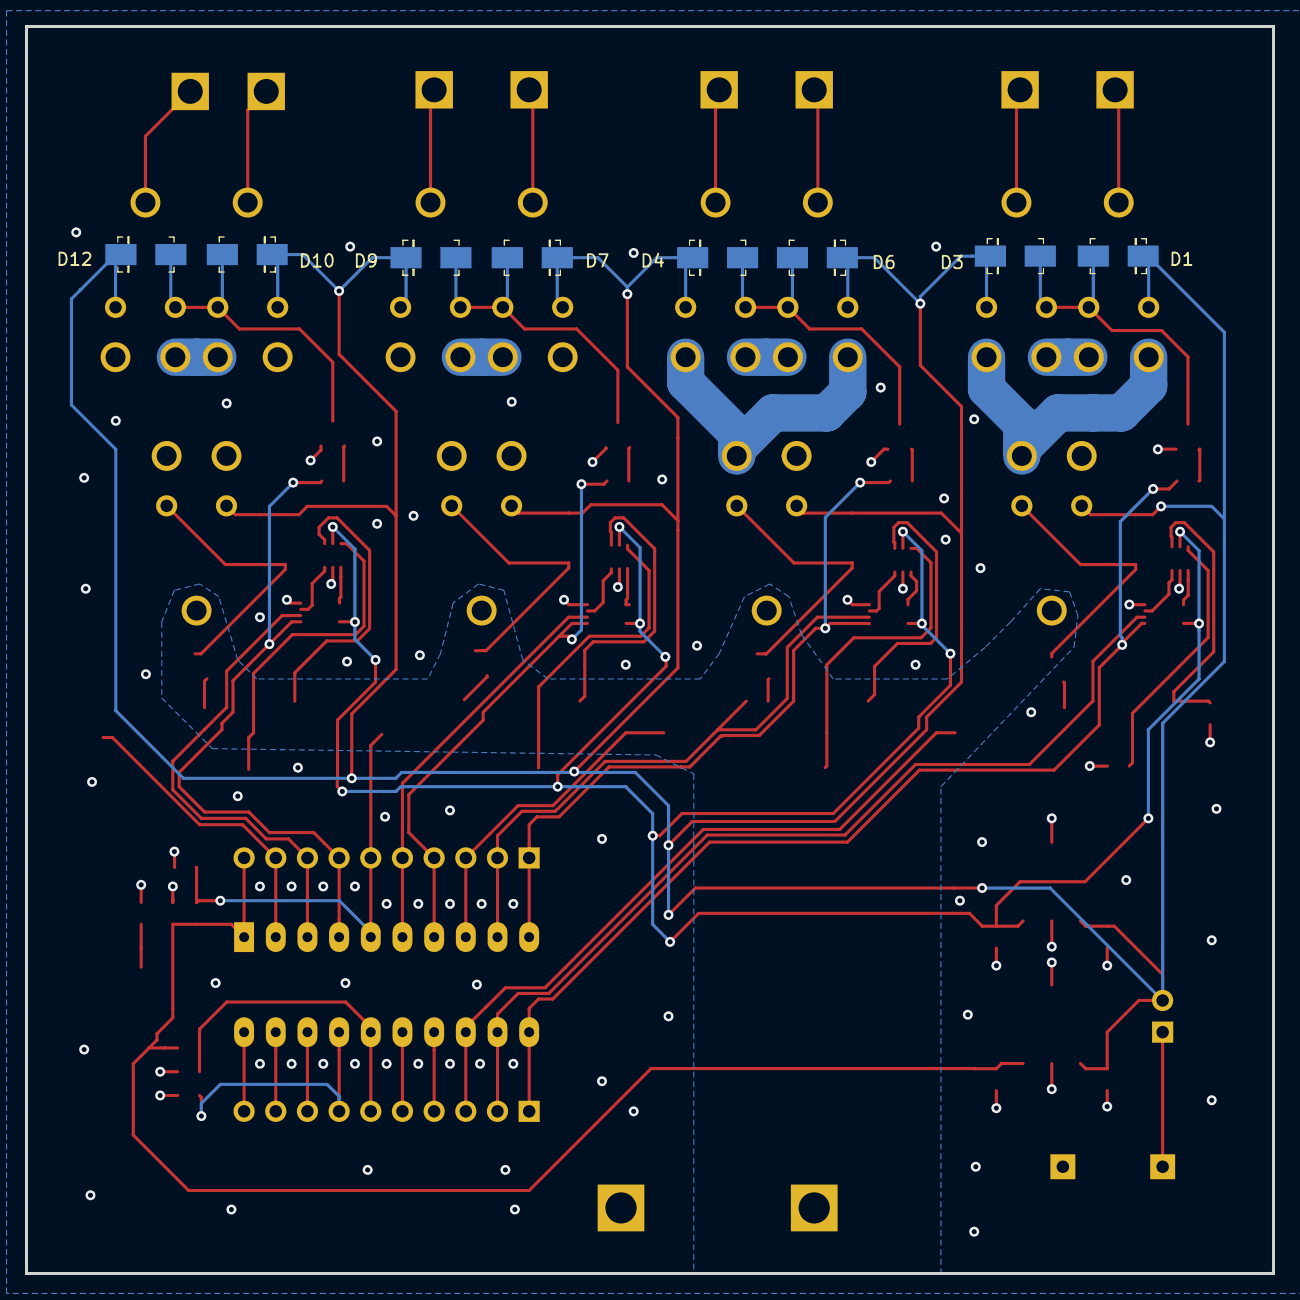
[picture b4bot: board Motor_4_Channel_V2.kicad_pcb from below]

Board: 2 copper layers, 100.0 x 100.0 mm, 93 parts (8 on the bottom side), 77 nets.

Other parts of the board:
R10: R; R_0603_1608Metric_Pad1.05x0.95mm_HandSolder

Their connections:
GND: R10.2; also elsewhere on the board
GREEN_4: R10.1; also elsewhere on the board

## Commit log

2018-07-26 Testing git...
2018-08-05 Created project for nrf52832. Created general library to add custom components.
2018-08-06 Added NRF52832 symbol to library and schematic
2018-08-15 Added nearly finished schematic and layout files for NRF52832.
2018-08-15 Removed unneeded capacitors from P0.25 and P0.26
2018-08-24 Added finished Arduino Nanite project
2018-11-15 Added personal 4-channel motor controller V1 and V2 project files
2018-11-21 Added power circuit for NRF52. Added SMT Practice V1 project. Modified Motor v2 project.
2018-11-22 Added digikey library. Started PCB layout for Motor 4 CH V2.
2018-11-24 Added progress to Motor 4 CH V2 layout.
2018-11-25 Initializing pull request for Motor_4CH_V2
2018-11-25 Added project for board that will have a buck converter and a boost converter.
2018-11-26 Switched THT 2-pin male headers for buttons and led with SMT headers. Rearranged SMT components,
2018-11-29 Added RC circuit to each button for hardware debouncing.
2018-11-29 Changed output Red/Green LED circuit to charlieplexing design.
2018-12-05 Misc. changes to Motor PCB.
2018-12-06 Added I2C components: 4KB EEPROM, Light sensor, and Temp sensor to schematic.
2018-12-07 Updated Boost conv. components and moved 3.3V regulator.
2018-12-07 Updated SWD interface headers
2018-12-07 Added LCD with SPI interface to schematic.
2018-12-07 Updated LCD circuit schematic.
2018-12-08 Added main power switch and LCD power switch. Added GPIO breakout pins.
2018-12-08 Added breakout pins for SWDIO and SWDCLK for test purposes.
2018-12-08 Set footprints for some components of battery charging circuit.
2018-12-09 Added Micro USB type B footprint
2018-12-09 Added SW_DPDT_Slide footprint. Finished updating footprints for all USB/Battery charger components.
2018-12-10 Finished boost converter and regulators footprint assignments.
2018-12-10 Added footprint for LCD and finished footprint assignments for LCD components.
2018-12-10 Finished footprint assignments for I2C components
2018-12-10 Finished foorprint assignments for GPIO pins, LEDs, and button.
2018-12-11 Finished footprint assignment for SWD Header and Reset button
2018-12-11 Added series resistors for SWDCLK, SWDIO, and SWO
2018-12-11 Finished footprint assignments for NRF52 base components
2018-12-12 Updated component placement for PCB layout
2018-12-12 Finished component placement on PCB layout. Ready for routing.
2018-12-12 Finished routing of components. Silkscreen labels still not finished.
2018-12-13 Finished adding silkscreen labels. Added 3 M2 mounting holes. Generated gerber files.
2018-12-14 Fixed wrong values for some components
2018-12-14 Added basic topologies for a buck converter and boost converter to schematic.
2018-12-18 Separated Buck converter and Boost converter projects.
2018-12-18 Added controller circuit
2018-12-23 Updated some component values
2018-12-23 Changed values for dead time control
2018-12-23 Removed unnecessary schottky diode label.
2018-12-26 Finished schematic. Changed compensation to Type 3. Added fuse to input. Finished adding values and footprints for all components.
2018-12-26 Finished component placement for PCB layout
2018-12-26 Finished PCB layout. Ready for Gerber files.
2018-12-26 Added schematic and PCB layout for USB Type A female connector breakout.
2018-12-28 Added schematic for a relay to control an outlet.
2018-12-31 Added footprints to resistors.
2018-12-31 Set footprints for flyback diode and mosfet
2019-01-01 Finished PCB layout. Generated BOM.
2019-01-01 Changed out+ and out- pads to be 7.62mm apart to make it easy to attach USB breakout board.
2019-01-01 Added rounded corners to PCB layout.
2019-01-01 Generated gerber files
2019-01-01 Changed footprint for PMOS switch. Generated gerber files.
2019-01-02 Created BOM file.
2019-01-02 Extra commit
2019-01-04 Generated gerber files.
2019-01-04 Renamed gerber zip file.
2019-01-05 Updating branch
2019-01-06 Updating rescue lib for NRF52 Reference.
2019-01-06 Fixed project library
2019-01-06 Created project for NRF52_V2
2019-01-06 Moved MM8130RA symbol to project library. Added power and base schematics from nrf52 V1
2019-01-06 Added fuses to USB power and battery. Modified low battery LED circuit.
2019-01-06 Added SWD header and some buttons
2019-01-06 Added GPIO pin headers, buttons, and LEDs.
2019-01-08 Added EEPROM 4KB and photo sensor to schematic.
2019-08-31 First commit. Added 18650_charger project file.
2019-09-01 Progress on charging circuit.
2020-01-17 Backlink to CADLAB.io has been added.
2020-08-10 Added new charging ICs and STM32 MCU for voltage measurement.
2020-08-16 Updates to MCU circuit
2020-08-17 Update to MCU circuit
2020-08-22 Updated STM32 schematic
